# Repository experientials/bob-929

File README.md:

# Bob

Bob is an independent device that sees and senses the environment. It recognises objects and behavior based on what it has been taught. You use it in the field to collect the vision of things. The collected vision is turned into Machine Vision Models that 
allows you to create real-world puzzles and games. This allows you to create physical games to be played with family and friends
only limited by your imagination.

<family playing dice game>

It receives stereo video input over 2 x 2-lane MIPI CSI2. Additionally it receives sensor input over I2C
for distance, color, brightness. The sensor inputs are processed and disected to identify objects, people and
behaviour. Ziloo can connect over USB to make the output available on your Laptop, Phone or the Internet.

## Machine Vision Camera

Bob can be used to capture things out in the world to learn how to recognising them in the future. You can do this simply by pressing the camera button on the side. While the button is pressed images will be captured of the thing. As you capture a thing from different angles and in different conditions the coverage will increase.

You could use a Smartphone or Professional camera to capture your training images. But you should capture images with a setup similar to what the Vision Model will be seeing when used.

### Camera Remote Control

Using a bluetooth module you can control Bob with a Smartphone App for capturing Visions.

### Facing the camera

You can show Bob an object and turn it around. Bob will capture the vision of the object for you to have later.

## Physical Game Development Kit

Example Board game Monopoly
Bob Store for Apps
Tutorial Videos

## Speaker Bundle

The bundle comes with a speaker module that you plug into Bob. This allows Bob to speak.
It also comes with 2 voices that allow the games to easily generate speach as part of the game mechanics.

## Games Bundle

The bundle comes with an Multiplayer Module that you plug into Bob to connecting it with Bob elsewhere to allow you to play with
more people. 
It comes with 5 fun games to play in your livingroom and garden.

## Professional level Edge Machine Vision; Batteries Included

To get the precision in Machine Vision powerful hardware is needed to run modern ML Models made with PyTorch and TensorFlow.
To run this you typically get a Development board that costs $300 - $400 and then add camera modules that cost $75 - $200.
This gives you very raw power, but it isn't made to be run on batteries. It draws much too much power.
We have made Bob from the beginning aimed at single Lithium-Ion cell voltage, and made it good at detecting when the save on
battery.

## Unattended Mode

Bob can run unattended to capture interesting visions based on what is already known. This means that it needs good privacy, allowing you to review what has been captured before it is potentially uploaded to cloud services. This is why Bob isn't connected to the Internet or WiFi by default. It can be made to run unattended and automatically upload data, but in order to do so you must plug in the networking hardware.

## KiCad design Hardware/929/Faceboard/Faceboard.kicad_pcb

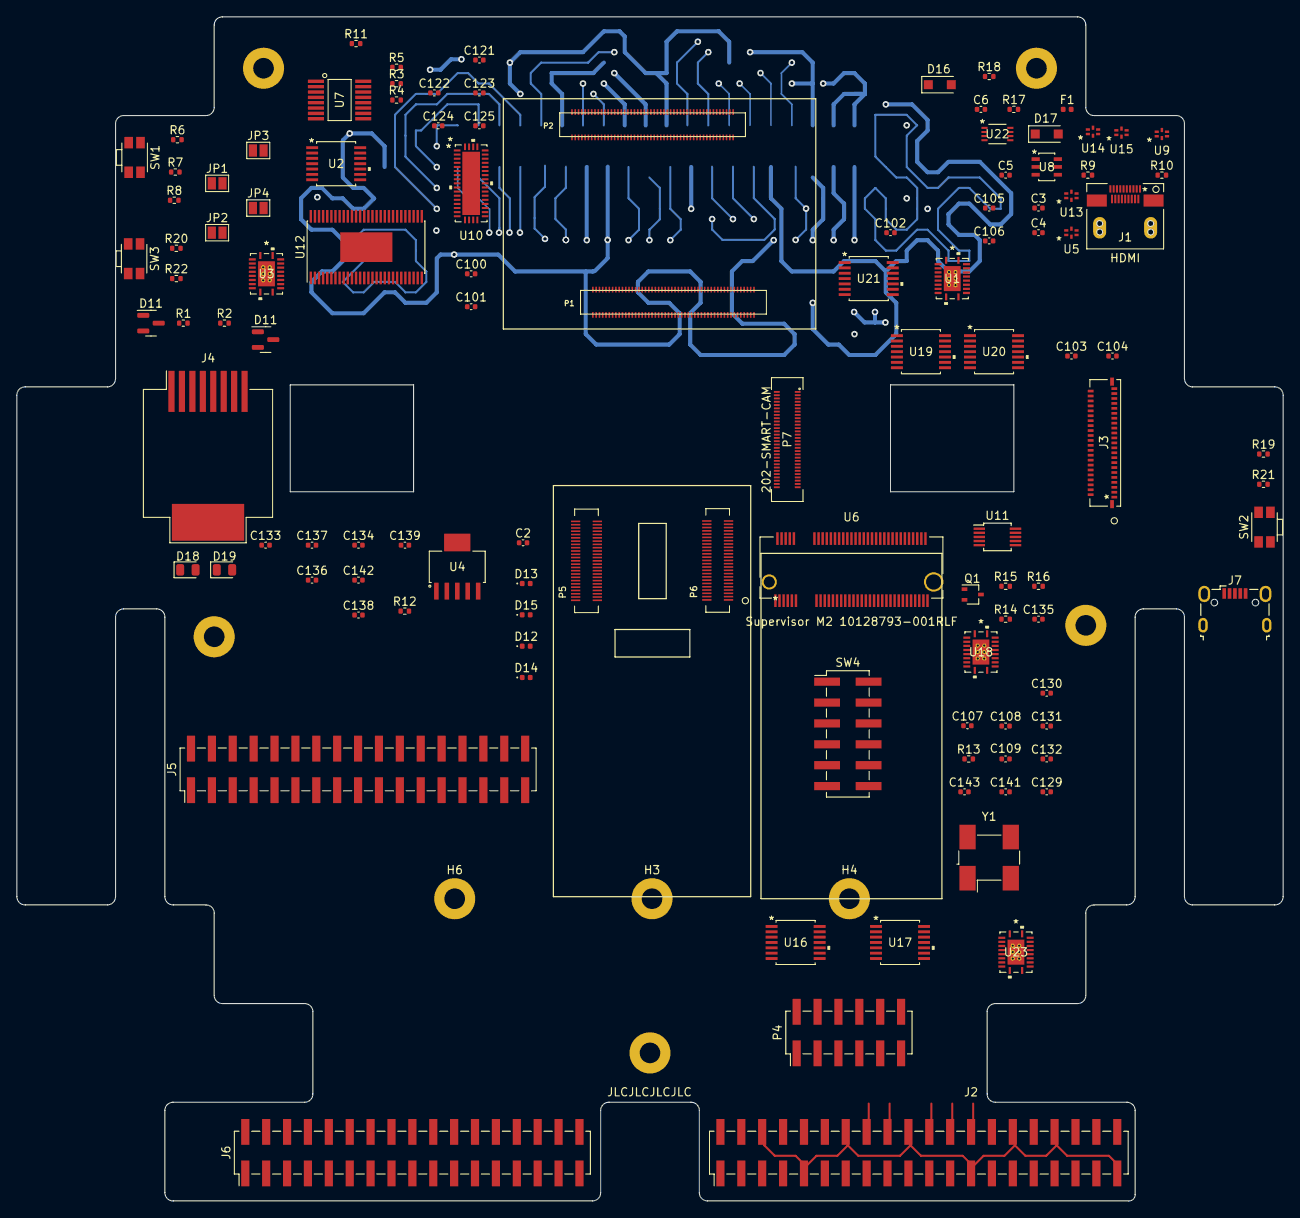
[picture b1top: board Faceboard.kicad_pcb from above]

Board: 4 copper layers, 154.0 x 144.0 mm, 122 parts (1 on the bottom side), 164 nets.

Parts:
C2: C; C_0402_1005Metric
C3, C4, C5, C121: 1uF; C_0402_1005Metric
C6, C100: 10nF; C_0402_1005Metric
C101, C102, C103, C104, C105, C106, C107, C108, C109, C122, C123, C124, C125, C133, C134, C141, C142: 100nF; C_0402_1005Metric
C129, C143: 27pF; C_0402_1005Metric
C130, C131, C137, C138, C139: 100uF; C_0402_1005Metric
C132, C136: 10uF; C_0402_1005Metric
C135: 100pF; C_0402_1005Metric
D11, D11#2: BAT54C; SOT-23
D12, D13, D14, D15: D; D_0402_1005Metric
D16, D17: 1A Schottky; D_SOD-123F
D18, D19: LED; LED_0805_2012Metric
F1: Polyfuse_Small; Fuse_0402_1005Metric
GPIO**: Front Face GPIO HEader; PinHeader_2x20_P2.54mm_Vertical_SMD
H1, H2, H3, H4, H5, H6, H7, H8: MountingHole; MountingHole_2.5mm_Pad
J1: HDMI; 467652301
J2: Raspberry_Pi_to_Ziloo; PinHeader_2x20_P2.54mm_Vertical_SMD
J3: Debug_4-2328724-5; 4-2328724-5
J4: RJ45; RJ45_Molex_0855135013_Vertical
J5: UCM-P20-misc; PinHeader_2x17_P2.54mm_Vertical_SMD
J6: UCM-P21-misc; PinHeader_2x17_P2.54mm_Vertical_SMD
J7: USB_B_Micro; USB_Micro-B_Wuerth_629105150521
JP1: TDO; SolderJumper-2_P1.3mm_Open_Pad1.0x1.5mm
JP2: TDI; SolderJumper-2_P1.3mm_Open_Pad1.0x1.5mm
JP3: SYS_SDA; SolderJumper-2_P1.3mm_Open_Pad1.0x1.5mm
JP4: SYS_SCL; SolderJumper-2_P1.3mm_Open_Pad1.0x1.5mm
P1: UCM-P1; HRS_DF40C-100DS-0.4V(51)
P2: UCM-P2; HRS_DF40C-100DS-0.4V(51)
P4: Power; PinHeader_2x06_P2.54mm_Vertical_SMD
P5: 292_PWRCTL-50; HRS_DF40C-50DS-0.4V(51)
P6: 292_HIGH-SPEED-50; HRS_DF40C-50DS-0.4V(51)
P7: 202-SMART-CAM; DF40C-60DS-0.4V51
Q1: 2SC4213; SOT-323_SC-70
R1, R2: 475Ohm; R_0402_1005Metric
R3, R4, R5: 10K; R_0402_1005Metric
R6, R8, R19, R20, R21, R22: 0R; R_0402_1005Metric
R7: DNP; R_0402_1005Metric
R9: 47K; R_0402_1005Metric
R10: 1K2; R_0402_1005Metric
R11: R; R_0402_1005Metric
R12: 10k; R_0402_1005Metric
R13: 1k; R_0402_1005Metric
R14: 100K; R_0402_1005Metric
R15, R16: 4.7K; R_0402_1005Metric
R17: 1K/1%; R_0402_1005Metric
R18: 200K; R_0402_1005Metric
SW1: Reset; SW_SPST_EVQP7A
SW2: Power; SW_SPST_EVQP7A
SW3: Alt. Boot; SW_SPST_EVQP7A
SW4: Power; PinHeader_2x06_P2.54mm_Vertical_SMD
U1, U3, U18, U23: SN74CB3Q3245RGYR
U2: SN74CBTLV3126PWR
U4: TPS79618DCQR
U5, U9, U13, U14, U15: LCFE121002H900TG
U6: Supervisor M2 10128793-001RLF; 10128793-001RLF
U7: TCA9534; TCA9534PWR
U8: IP4220CZ6
U10: CBTL04083ABS_518
U11: FSUSB42MUX; MSOP-10_3x3mm_P0.5mm
U12: Faceboard_Expander_FR2032IG56; HTSSOP-56-1EP_6.1x14mm_P0.5mm_EP3.61x6.35mm
U16, U17, U19, U20, U21: TXS0104EPWR
U22: PCA9306DCUR
Y1: 25.000MHz; Oscillator_SMD_Abracon_ASV-4Pin_7.0x5.1mm_HandSoldering

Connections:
/C_EX_RXD: P1.86 (UART4_TXD), U1.12 (B7)
/C_EX_TXD: P1.84 (UART4_RXD), U1.11 (B8)
/Camera + Sound Domain/I2S_1V8_RXC: P7.54 (I2S_SCK), U19.2 (A1)
/Camera + Sound Domain/I2S_1V8_RXD1: P7.50 (I2S_D1), U19.4 (A3)
/Camera + Sound Domain/I2S_1V8_RXD2: P7.48 (I2S_D2), U19.5 (A4)
/Camera + Sound Domain/I2S_1V8_RXFS: P7.52 (I2S_LRCLK), U19.3 (A2)
/Camera + Sound Domain/OE_SOUND: P7.41 (OE_SOUND), U19.8 (OE), U20.8 (OE), U21.8 (OE)
/Ethernet and SD1/ETH0_LED_1000: D11.1, D11#2.1
/Ethernet and SD1/ETH0_LINK_LED: D11.2, D11#2.2
/Ethernet and SD1/RPI_3V3: J2.1 (3V3), J2.17 (3V3), P4.10
/Ethernet and SD1/RPI_5V: J2.2 (5V), J2.4 (5V), P4.8
/Ethernet and SD1/SD1_CLK: J2.15 (GPIO22/SDIO_CLK), J5.15 (SD1_CLK)
/Ethernet and SD1/SD1_CMD: J2.16 (GPIO23/SDIO_CMD), J5.17 (SD1_CMD)
/Ethernet and SD1/SD1_DATA0: J2.18 (GPIO24/SDIO_DAT0), J5.24 (SD1_DATA0)
/Ethernet and SD1/SD1_DATA1: J2.22 (GPIO25/SDIO_DAT1), J5.22 (SD1_DATA1)
/Ethernet and SD1/SD1_DATA2: J2.37 (GPIO26/SDIO_DAT2), J5.21 (SD1_DATA2)
/Ethernet and SD1/SD1_DATA3: J2.13 (GPIO27/SDIO_DAT3), J5.23 (SD1_DATA3)
/Ethernet and SD1/STEM_I2C_SCL: J2.5 (STEM_SCL/GPIO3), J5.33 (STEM_SCL)
/Ethernet and SD1/STEM_I2C_SDA: J2.3 (STEM_SDA/GPIO2), J5.34 (STEM_SDA)
/Ethernet and SD1/SYS_I2C_SCL: J2.28 (SYS_SCL/GPIO1), J6.7 (SYS_I2C_SCL)
/Ethernet and SD1/SYS_I2C_SDA: J2.27 (SYS_SDA/GPIO0), J6.5 (SYS_I2C_SDA)
/Ethernet and SD1/SYS_PRG#: J5.30 (SYS_PRG), U23.19 (*OE)
/Ethernet and SD1/UCM_3V3: J5.7 (3V3), P4.4
/Ethernet and SD1/UCM_5V: J5.6 (5V0), P4.2
/Expander, M.2 and T-USB/3V3_TU: P5.40 (3V3), P5.43 (3V3), SW4.8
/Expander, M.2 and T-USB/5V_TU: P5.46 (5V), SW4.6
/Expander, M.2 and T-USB/ALT_BOOT: J3.19, R20.1, U12.10 (ALT_BOOT/P4.4)
/Expander, M.2 and T-USB/BAT_CE: P5.24 (BAT_CE#), U12.39 (P2.3)
/Expander, M.2 and T-USB/BAT_EN: P5.25 (BAT_EN), U12.38 (P2.4)
/Expander, M.2 and T-USB/BAT_INT: JP4.1 (A), P5.23 (BAT_INT)
/Expander, M.2 and T-USB/B_PCIE_WAKE: U7.6 (P2), U12.49 (B_PCIE_WAKE/P3.7)
/Expander, M.2 and T-USB/FACE_FW_RXD: J3.33, U12.27 (UART1_RX/FW_RX/A1/Vref+/P1.1)
/Expander, M.2 and T-USB/FACE_FW_TXD: J3.32, U12.28 (FW_TXD/A0/Vref-/P1.0)
/Expander, M.2 and T-USB/FACE_RST: J3.15, J3.31, U12.16 (~RST/NMI/SBWTDIO)
/Expander, M.2 and T-USB/FACE_SBWTCK: J3.30, U12.17 (TEST/SBWTCK)
/Expander, M.2 and T-USB/FACE_TCK: J3.11, JP4.2 (B), U12.24 (TCK/A4/VREF+/P1.4)
/Expander, M.2 and T-USB/FACE_TDI: J3.13, JP2.2 (B), U12.22 (TA0.2/TDI/TCLK/A6/P1.6)
/Expander, M.2 and T-USB/FACE_TDO: J3.14, JP1.2 (B), U12.21 (TA0.1/TDO/A7/P1.7)
/Expander, M.2 and T-USB/FACE_TMS: J3.12, JP3.2 (B), U12.23 (TMS/A5/P1.5)
/Expander, M.2 and T-USB/FLASH_HOLD: J3.5, P5.34 (FLASH_HOLD)
/Expander, M.2 and T-USB/F_SBWTCK: U3.2 (A1), U3.18 (B1)
/Expander, M.2 and T-USB/F_SBWTDIO: U3.3 (A2), U3.17 (B2)
/Expander, M.2 and T-USB/LOCK_BTN: P5.28 (LOCK_BTN), U12.9 (P4.5)
/Expander, M.2 and T-USB/M2B_PERST: U7.4 (P0), U12.56 (M2B_PERST/P3.0)
/Expander, M.2 and T-USB/M2B_USB_MUX: U7.9 (P4), U10.9 (SEL), U12.50 (M2B_USB_MUX/P3.6)
/Expander, M.2 and T-USB/M.2 Key B connector/PCIE_CLGEN_X1: C143.1, Y1.1
/Expander, M.2 and T-USB/M.2 Key B connector/PCIE_CLGEN_X2: C129.1, Y1.3
/Expander, M.2 and T-USB/MCU_SYS_INT: P5.12 (SYS_PD_CTL_INT), U12.13 (P4.1/XIN)
/Expander, M.2 and T-USB/PD_HRESET: J3.23, P5.39 (PD_HRESET), U12.35 (P2.7)
/Expander, M.2 and T-USB/PD_USBC_INT: P5.38 (USB1_PLUG_INT), U7.13 (~INT), U12.18 (TA1.1/P4.0)
/Expander, M.2 and T-USB/POR_B_3P3: R7.1, U12.40 (POR_B_3P3/P2.2)
/Expander, M.2 and T-USB/POWER_PD_CTL_INT: JP3.1 (A), P5.37 (POWER_PD_CTL_INT)
/Expander, M.2 and T-USB/POWER_SCL: J3.40, P5.36 (POWER_SCL), U2.2 (1A), U2.9 (3A), U12.5 (P7.1)
/Expander, M.2 and T-USB/POWER_SDA: J3.41, P5.35 (POWER_SDA), U2.5 (2A), U2.12 (4A), U12.4 (P7.2)
/Expander, M.2 and T-USB/POWER_TO_STEM: U2.10 (3OE), U2.13 (4OE), U12.19 (TA1.2/P8.3)
/Expander, M.2 and T-USB/POWER_TO_SYS: U2.1 (1OE), U2.4 (2OE), U12.20 (TA1CLK/P8.2)
/Expander, M.2 and T-USB/PWRBTN: J3.17, R19.1, U12.11 (PWRBTN/P4.3)
/Expander, M.2 and T-USB/PWR_CHARGE: D12.1 (K), P6.30 (PWR_CHARGE)
/Expander, M.2 and T-USB/PWR_CHARGE_LESS_1V4: D14.2 (A), U12.26 (CHARGE_LESS_1V4/UART1_TX/A2/P1.2)
/Expander, M.2 and T-USB/SBU1: J3.28, P5.9 (USB1_SBU1)
/Expander, M.2 and T-USB/SBU2: J3.29, P5.10 (USB1_SBU2)
/Expander, M.2 and T-USB/SHUTDOWN_BTN: P5.27 (SHUTDOWN_BTN), U12.8 (P4.6)
/Expander, M.2 and T-USB/SPI2_CLK: J3.1, P5.32 (SPI_CLK)
/Expander, M.2 and T-USB/SPI2_MISO: J3.2, P5.31 (SPI_MISO)
/Expander, M.2 and T-USB/SPI2_MOSI: J3.3, P5.30 (SPI_MOSI)
/Expander, M.2 and T-USB/STEM_I2C_SCL: J3.44, P6.17 (STEM_SCL), U2.8 (3B), U12.31 (UCB0SIMO/STEM_SCL/P5.3)
/Expander, M.2 and T-USB/STEM_I2C_SDA: J3.45, P6.18 (STEM_SDA), U2.11 (4B), U12.32 (UCB0SIMO/STEM_SDA/P5.2)
/Expander, M.2 and T-USB/STEM_INT: P6.19 (STEM_MSG), U12.12 (P4.2/XOUT)
/Expander, M.2 and T-USB/SYS_I2C_SCL: J3.42, P5.13 (SYS_I2C_SCL), U2.3 (1B), U7.14 (SCL), U12.33 (UCB0CLK/SYS_SCL/P5.1)
/Expander, M.2 and T-USB/SYS_I2C_SDA: J3.43, P5.14 (SYS_I2C_SDA), U2.6 (2B), U7.15 (SDA), U12.34 (UCB0STE/SYS_SDA/P5.0)
/Expander, M.2 and T-USB/SYS_RST_PMIC: J3.18, R6.1, U12.7 (SYS_RST_PMIC/P4.7)
/Expander, M.2 and T-USB/T-USB_SPI_CS: J3.4, P5.33 (SPI_CS), U12.36 (T-USB_SPI_CS/P2.6)
/Expander, M.2 and T-USB/T_SBWTCK: U3.6 (A5), U3.14 (B5)
/Expander, M.2 and T-USB/T_SBWTDIO: U3.7 (A6), U3.13 (B6)
/Expander, M.2 and T-USB/USB_XD_OE: P5.16 (USB_XD_OE), U12.52 (SH1_STCP/P3.4)
/Expander, M.2 and T-USB/USB_XD_SEL: P5.17 (USB_XD_SEL), U12.51 (SH2_STCP/P3.5)
/Expander, M.2 and T-USB/VCC_RTC_TU: P5.49 (VCC_RTC), SW4.10
/Expander, M.2 and T-USB/VSOM_LESS_1V4: D15.2 (A), U12.25 (VSOM_LESS_1V4/A3/P1.3)
/Expander, M.2 and T-USB/VSOM_TU: P5.1 (VSOM), P5.15 (VSOM), P5.26 (VSOM), P6.1 (VSOM), P6.26 (VSOM), P6.36 (VSOM), P6.39 (VSOM), P6.42 (VSOM), P6.45 (VSOM), P6.48 (VSOM), SW4.2, SW4.4
/F_EX_RXD: P1.74 (UART2_TXD), U1.16 (B3)
/F_EX_TXD: P1.76 (UART2_RXD), U1.15 (B4)
/HDMI socket/5V_POWER: C6.1, D17.1 (K), J1.19 (+5V_POWER), R9.1, R10.1, R17.1, R18.1, U8.1 (I/O_1), U8.5 (VP)
/HDMI socket/DDC_SCL: J1.17 (SCL), U8.4 (I/O_3), U22.6 (SCL2)
/HDMI socket/DDC_SDA: J1.18 (SDA), U8.3 (I/O_2), U22.5 (SDA2)
/HDMI socket/HDMI_CEC: D16.1 (K), J1.15 (CEC), U8.6 (I/O_4)
/I2C5_SCL: P1.100 (I2C5_SCL), U1.18 (B1)
/I2C5_SDA: P1.96 (I2C5_SDA), U1.17 (B2)
/I2C6_SCL: P1.87 (I2C6_SCL), U1.14 (B5)
/I2C6_SDA: P1.89 (I2C6_SDA), U1.13 (B6)
/SYS_PRG#: P2.69 (SYS_PRG#/4_17), U1.19 (*OE)
CAM_1V8: C103.1, C105.1, C107.1, P7.12 (1V8), P7.30 (1V8), U4.4 (OUT), U19.14 (VCCB), U20.14 (VCCB), U21.14 (VCCB)
GND: C5.2, C6.2, C100.2, C101.2, C102.1, C103.2, C104.2, C105.2, C106.2, C107.2, C108.2, C109.2, C121.1, C122.1, C123.1, C124.1, C125.1, C129.2, C130.2, C131.2, C132.2, C133.2, C134.2, C135.2, C136.2, C137.2, C138.2, C139.2, C141.2, C142.2, C143.2, J1.4 (TMDS_DATA2_SHIELD), J1.7 (TMDS_DATA1_SHIELD), J1.10 (TMDS_DATA0_SHIELD), J1.13 (TMDS_CLOCK_SHIELD), J2.6 (GND), J2.9 (GND), J2.14 (GND), J2.20 (GND), J2.25 (GND), J2.30 (GND), J2.34 (GND), J2.39 (GND), J3.7, J3.10, J5.31 (GND), J5.32 (GND), J6.6 (GND), J6.9 (GND), J7.5 (GND), J7.6 (Shield), P1.4 (GND), P1.10 (GND), P1.20 (GND), P1.40 (GND), P1.54 (GND), P1.64 (GND), P1.78 (GND), P1.88 (GND), P2.10 (GND), P2.16 (GND), P2.22 (GND), P2.28 (GND), P2.34 (GND), P2.40 (GND), P2.46 (GND), P2.54 (GND), P2.72 (GND), P2.82 (GND), P4.11, P4.12, P5.2 (GND), P5.5 (GND), P5.8 (GND), P5.11 (GND), P6.4 (GND), P6.7 (GND), P6.10 (GND), P6.13 (GND), P6.16 (GND), P6.20 (GND), P6.23 (GND), P6.33 (GND), Q1.2 (E), R1.2, R2.2, R4.2, R8.2, R9.2, R16.2, R17.2, R21.2, SW4.11, SW4.12, U1.10 (GND), U2.7 (GND), U3.10 (GND), U4.3 (GND), U5.5, U5.6, U6.3 (GND), U6.5 (GND), U6.27 (GND), U6.33 (GND), U6.39 (GND), U6.45 (GND), U6.51 (GND), U6.57 (GND), U7.8 (GND), U8.2 (GND), U9.5, U9.6, U10.1 (GND), U10.4 (GND), U10.10 (GND), U10.21 (GND), U10.39 (GND), U10.41 (XSD01), U10.43 (GND), U11.5 (GND), U11.10 (~OE), U12.14 (DVSS), U13.5, U13.6, U14.5, U14.6, U15.5, U15.6, U16.7 (GND), U17.7 (GND), U18.10 (GND), U19.7 (GND), U20.7 (GND), U21.7 (GND), U22.1 (GND), U23.10 (GND), Y1.2, Y1.4
HDMI_5V: F1.1, P4.1, P4.7, SW4.5
LIVE_1V8: C133.1, C141.1, U16.14 (VCCB), U17.14 (VCCB)
LIVE_3V3: C121.2, C122.2, C123.2, C124.2, C125.2, C130.1, C131.1, C132.1, C134.1, C136.1, C137.1, C138.1, C139.1, C142.1, D16.2 (A), P4.3, P4.9, R3.1, R5.1, R11.1, R12.2, R13.2, R14.1, R22.1, SW4.7, U6.2 (3V3), U6.70 (3V3), U6.72 (3V3), U6.74 (3V3), U7.16 (VDD), U10.5 (VDD), U10.8 (VDD), U10.13 (VDD), U10.18 (VDD), U10.20 (VDD), U10.30 (VDD), U10.40 (VDD), U10.42 (VDD), U11.1 (VCC), U16.1 (VCCA), U17.1 (VCCA), U18.20 (VCC), U22.2 (VREF1)
unnamed: C2.1, U4.5 (NR/FB)
unnamed: C3.2, R10.2, U5.2
unnamed: C4.2, U5.1
unnamed: C5.1, D17.2 (A), F1.2
unnamed: C102.2, P1.55 (PHY_2V5_OUT)
unnamed: C135.1, Q1.3 (C), R14.2, U6.67 (RESET)
unnamed: D11.3, D11#2.3, D19.2 (A)
unnamed: D12.2 (A), D14.1 (K)
unnamed: D13.2 (A), D15.1 (K)
unnamed: D18.1 (K), R1.1
unnamed: D19.1 (K), R2.1
unnamed: J1.1 (HOT_PLUG_DETECT), U5.3
unnamed: J1.2 (UTILITY), U5.4
unnamed: J1.3 (TMDS_DATA2+), U9.2
unnamed: J1.5 (TMDS_DATA2-), U9.1
unnamed: J1.6 (TMDS_DATA1+), U14.2
unnamed: J1.8 (TMDS_DATA1-), U14.1
unnamed: J1.9 (TMDS_DATA0+), U13.2
unnamed: J1.11 (TMDS_DATA0-), U13.1
unnamed: J1.12 (TMDS_CLOCK+), U15.2
unnamed: J1.14 (TMDS_CLOCK-), U15.1
unnamed: J2.8 (GPIO14/UART1_TXD), U23.4 (A3)
unnamed: J2.10 (GPIO15/UART1_RXD), U23.5 (A4)
unnamed: J2.32 (UART3_TX/GPIO12), U23.8 (A7)
unnamed: J2.33 (UART3_RX/GPIO13), U23.9 (A8)
unnamed: J3.24, P5.48 (USB1_XDP)
unnamed: J3.25, P5.47 (USB1_XDN)
unnamed: J3.26, P5.45 (USB2_XDP)
unnamed: J3.27, P5.44 (USB2_XDN)
unnamed: C100.1, C101.1, P1.62 (UCM_AVDD33_ETH)
unnamed: P5.6 (USB2_DP), U11.9 (HSD2+)
unnamed: P5.7 (USB2_DN), U11.8 (HSD2-)
unnamed: P6.8 (USB2_RX_DP), U10.38 (B0_P)
unnamed: P6.9 (USB2_RX_DN), U10.37 (B0_N)
unnamed: P6.11 (USB2_TX_DP), U10.36 (B1_P)
unnamed: P6.12 (USB2_TX_DN), U10.35 (B1_N)
unnamed: P7.5 (GND), P7.11 (GND), P7.17 (GND), P7.18 (GND), P7.23 (GND), P7.29 (GND), P7.56 (GND)
unnamed: Q1.1 (B), R15.2, R16.1
unnamed: R3.2, U7.3 (A2)
unnamed: R4.1, U7.1 (A0)
unnamed: R5.2, U7.2 (A1)
unnamed: R6.2, R7.2, SW1.1
unnamed: R8.1, SW1.2
unnamed: R11.2, U10.19 (XSD23)
unnamed: R12.1, U6.8 (W_DISABL1)
unnamed: R13.1, U6.6 (PWR_OFF)
unnamed: R18.2, U22.7 (VREF2), U22.8 (EN)
unnamed: R19.2, SW2.1
unnamed: R20.2, SW3.1
unnamed: R21.1, SW2.2
unnamed: R22.2, SW3.2
unnamed: U6.48 (GPIO_4), U16.2 (A1)
unnamed: U6.60 (COEX3), U16.3 (A2)
unnamed: U6.62 (M2B_UART_TXD), U16.4 (A3)
unnamed: U6.64 (M2B_UART_RXD), U16.5 (A4)
unnamed: U6.40 (STEM_SCL), U17.2 (A1)
unnamed: U6.42 (STEM_SDA), U17.3 (A2)
unnamed: U6.44 (GNSS_IRQ), U17.4 (A3)
unnamed: U6.46 (GPIO_3), U17.5 (A4)
unnamed: U6.56 (MFG_DAT), U18.11 (B8)
unnamed: U6.58 (MFG_CLK), U18.12 (B7)
unnamed: U6.66 (DETECT/CMD), U18.13 (B6)
unnamed: U6.68 (SUSCLK/SDCLK), U18.14 (B5)
unnamed: U6.65 (SD2_DATA3), U18.15 (B4)
unnamed: U6.63 (SD2_DATA2), U18.16 (B3)
unnamed: U6.61 (SD2_DATA1), U18.17 (B2)
unnamed: U6.59 (SD2_DATA0), U18.18 (B1)
SLEEP_3V3: C104.1, C106.1, C108.1, J3.16, J3.20, P1.93 (VCC_RTC), P7.6 (3V3), P7.24 (3V3), SW4.9, U1.20 (VCC), U2.14 (VCC), U4.1 (EN), U4.2 (IN), U19.1 (VCCA), U20.1 (VCCA), U21.1 (VCCA), U23.20 (VCC)
VSOM: D13.1 (K), P1.11 (V_SOM), P1.27 (V_SOM), P1.43 (V_SOM), P1.57 (V_SOM), P1.69 (V_SOM), P1.83 (V_SOM), P2.9 (V_SOM), P2.19 (V_SOM), P2.29 (V_SOM), P2.39 (V_SOM), P2.57 (V_SOM), P2.71 (V_SOM), P2.87 (V_SOM), SW4.1, SW4.3

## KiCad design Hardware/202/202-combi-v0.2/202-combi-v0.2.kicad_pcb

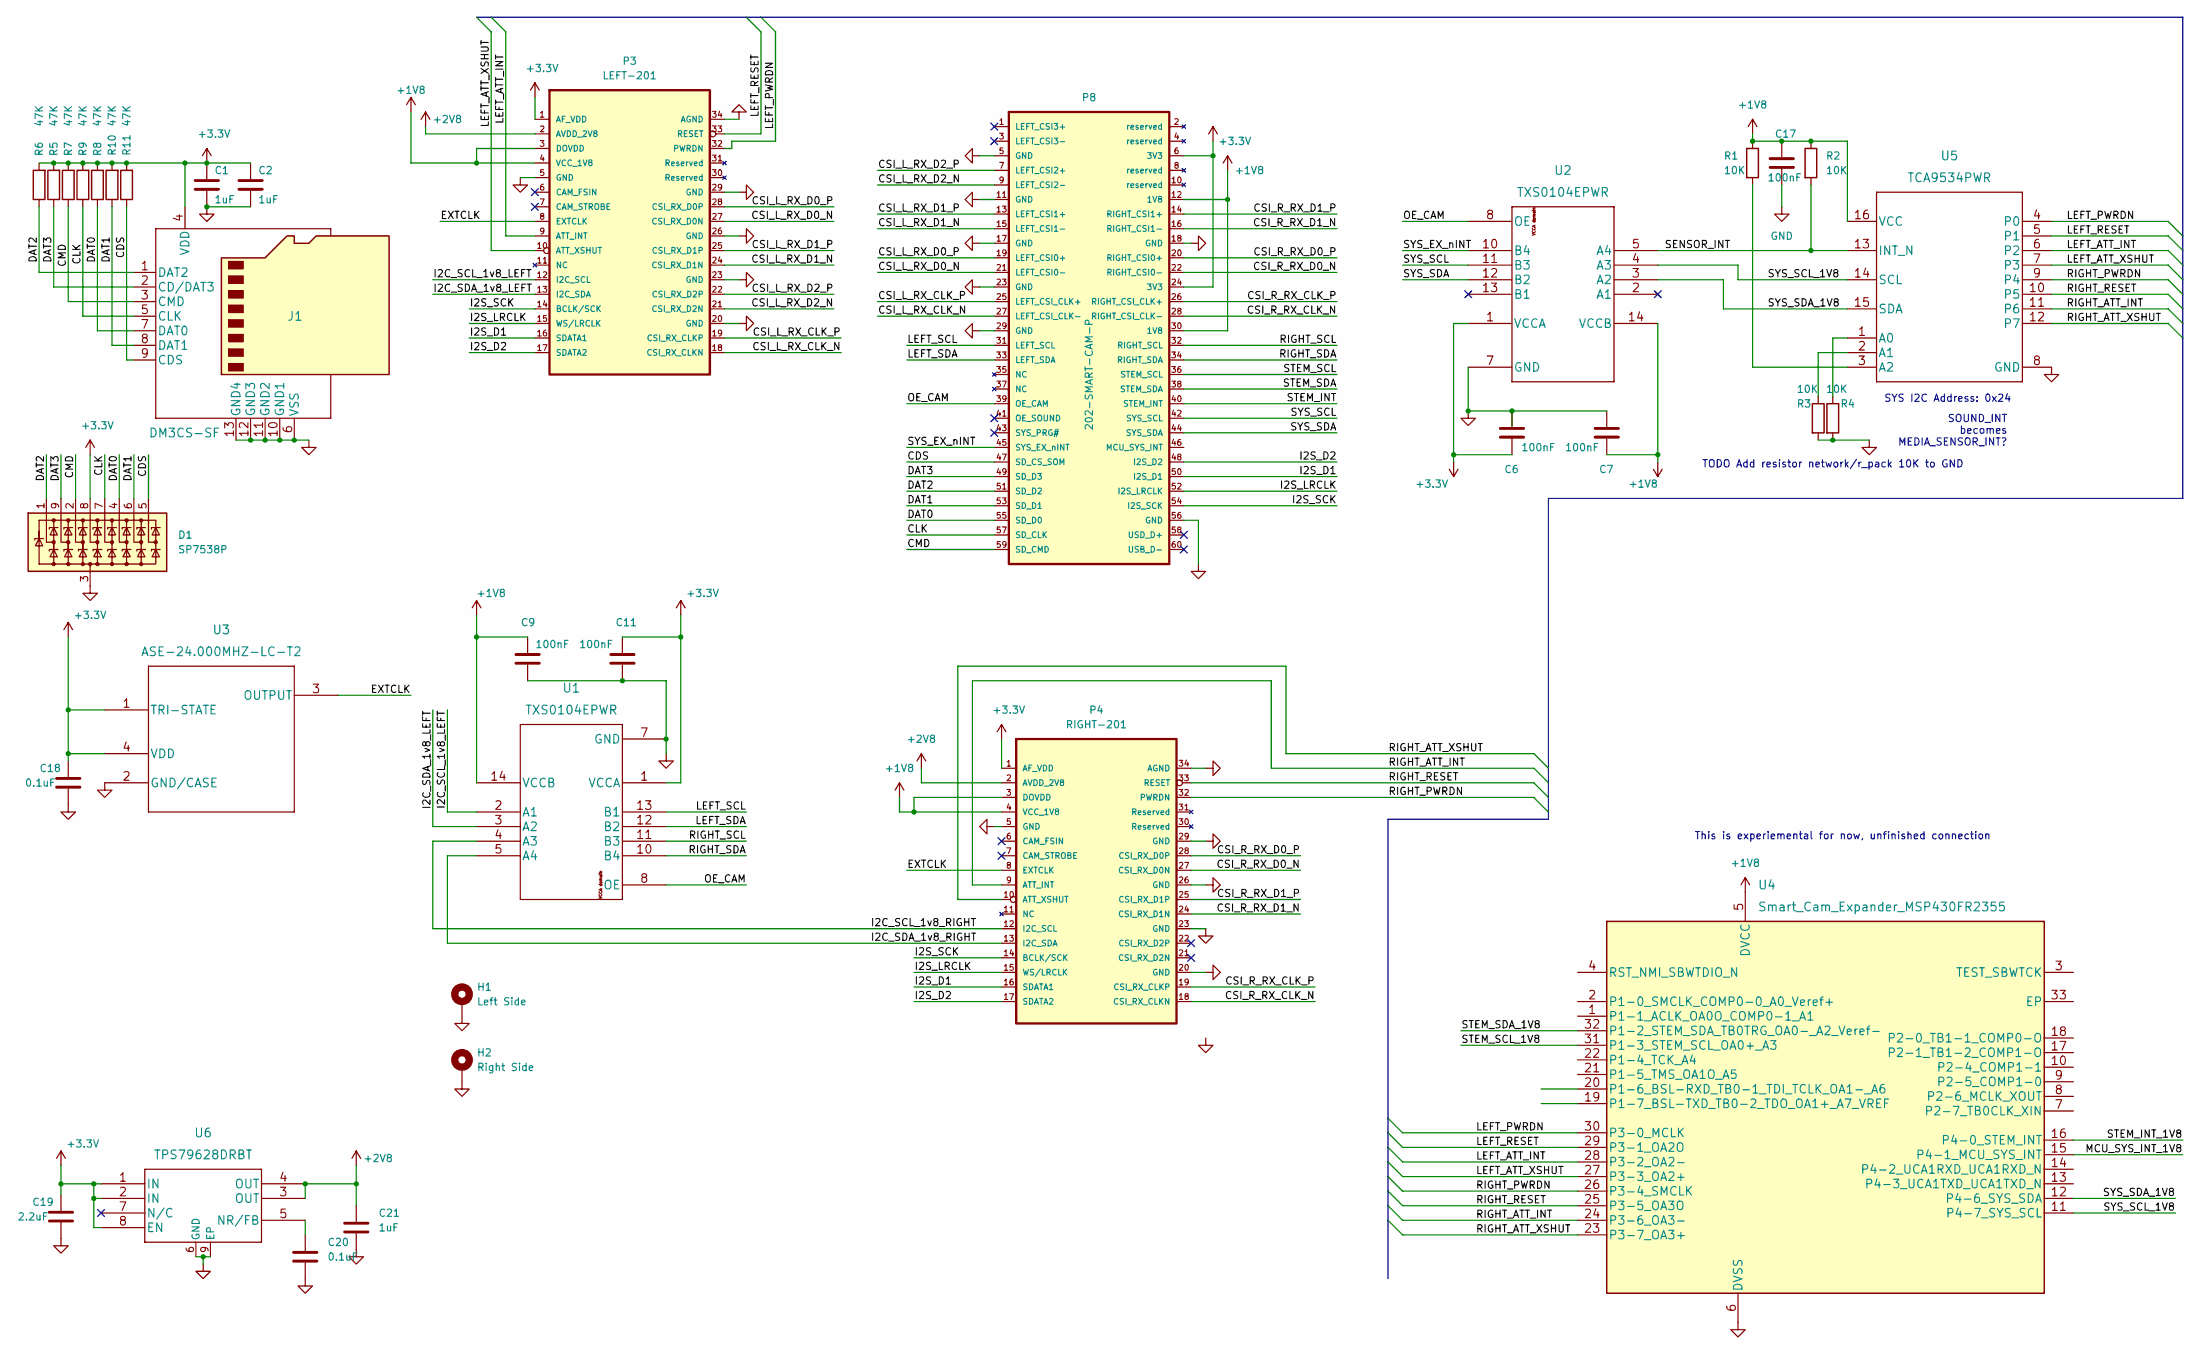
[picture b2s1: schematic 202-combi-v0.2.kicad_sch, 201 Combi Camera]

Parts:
C1, C2, C21: 1uF; C_0402_1005Metric
C6, C7, C9, C11, C17: 100nF; C_0402_1005Metric
C18, C20: 0.1uF; C_0402_1005Metric
C19: 2.2uF; C_0402_1005Metric
D1: SP7538P; UDFN-9_1.0x3.8mm_P0.5mm
H1: Left Side; MountingHole_2.2mm_M2
H2: Right Side; MountingHole_2.2mm_M2
J1: DM3CS-SF
P3: LEFT-201; HIROSE_DF40C-34DS-0.4V(51)_corrected
P4: RIGHT-201; HIROSE_DF40C-34DS-0.4V(51)_corrected
P8: 202-SMART-CAM-P; DF40C-60DP-0.4V51
R1, R2, R3, R4: 10K; R_0402_1005Metric
R5, R6, R7, R8, R9, R10, R11: 47K; R_0402_1005Metric
U1, U2: TXS0104EPWR; SSOP-14_5.3x6.2mm_P0.65mm
U3: ASE-24.000MHZ-LC-T2
U4: Smart_Cam_Expander_MSP430FR2355; MSP430FR2355TRSMR
U5: TCA9534PWR
U6: TPS79628DRBT; DFN-8-1EP_3x3mm_P0.65mm_EP1.7x2.05mm

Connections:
+1V8: C7.1, C9.1, C17.2, P3.3 (DOVDD), P3.4 (VCC_1V8), P4.3 (DOVDD), P4.4 (VCC_1V8), P8.12 (1V8), P8.30 (1V8), R1.1, R2.1, U1.14 (VCCB), U2.14 (VCCB), U4.5 (DVCC), U5.16 (VCC)
+2V8: C21.1, P3.2 (AVDD_2V8), P4.2 (AVDD_2V8), U6.3 (OUT), U6.4 (OUT)
+3.3V: C1.2, C2.2, C6.1, C11.1, C18.1, C19.1, D1.8 (K7), J1.4 (VDD), P3.1 (AF_VDD), P4.1 (AF_VDD), P8.6 (3V3), P8.24 (3V3), R5.2, R6.2, R7.2, R8.2, R9.2, R10.2, R11.2, U1.1 (VCCA), U2.1 (VCCA), U3.1 (TRI-STATE), U3.4 (VDD), U6.1 (IN), U6.2 (IN), U6.8 (EN)
/CDS: D1.5 (K4), J1.9 (CDS), P8.47 (SD_CS_SOM), R11.1
/CLK: D1.7 (K6), J1.5 (CLK), P8.57 (SD_CLK), R8.1
/CMD: D1.2 (K2), J1.3 (CMD), P8.59 (SD_CMD), R7.1
/CSI_L_RX_CLK_N: P3.18 (CSI_RX_CLKN), P8.27 (LEFT_CSI_CLK-)
/CSI_L_RX_CLK_P: P3.19 (CSI_RX_CLKP), P8.25 (LEFT_CSI_CLK+)
/CSI_L_RX_D0_N: P3.27 (CSI_RX_D0N), P8.21 (LEFT_CSI0-)
/CSI_L_RX_D0_P: P3.28 (CSI_RX_D0P), P8.19 (LEFT_CSI0+)
/CSI_L_RX_D1_N: P3.24 (CSI_RX_D1N), P8.15 (LEFT_CSI1-)
/CSI_L_RX_D1_P: P3.25 (CSI_RX_D1P), P8.13 (LEFT_CSI1+)
/CSI_L_RX_D2_N: P3.21 (CSI_RX_D2N), P8.9 (LEFT_CSI2-)
/CSI_L_RX_D2_P: P3.22 (CSI_RX_D2P), P8.7 (LEFT_CSI2+)
/CSI_R_RX_CLK_N: P4.18 (CSI_RX_CLKN), P8.28 (RIGHT_CSI_CLK-)
/CSI_R_RX_CLK_P: P4.19 (CSI_RX_CLKP), P8.26 (RIGHT_CSI_CLK+)
/CSI_R_RX_D0_N: P4.27 (CSI_RX_D0N), P8.22 (RIGHT_CSI0-)
/CSI_R_RX_D0_P: P4.28 (CSI_RX_D0P), P8.20 (RIGHT_CSI0+)
/CSI_R_RX_D1_N: P4.24 (CSI_RX_D1N), P8.16 (RIGHT_CSI1-)
/CSI_R_RX_D1_P: P4.25 (CSI_RX_D1P), P8.14 (RIGHT_CSI1+)
/DAT0: D1.4 (K3), J1.7 (DAT0), P8.55 (SD_D0), R9.1
/DAT1: D1.6 (K5), J1.8 (DAT1), P8.53 (SD_D1), R10.1
/DAT2: D1.1 (K1), J1.1 (DAT2), P8.51 (SD_D2), R5.1
/DAT3: D1.9 (K8), J1.2 (CD/DAT3), P8.49 (SD_D3), R6.1
/EXTCLK: P3.8 (EXTCLK), P4.8 (EXTCLK), U3.3 (OUTPUT)
/I2C_SCL_1v8_LEFT: P3.12 (I2C_SCL), U1.2 (A1)
/I2C_SCL_1v8_RIGHT: P4.12 (I2C_SCL), U1.4 (A3)
/I2C_SDA_1v8_LEFT: P3.13 (I2C_SDA), U1.3 (A2)
/I2C_SDA_1v8_RIGHT: P4.13 (I2C_SDA), U1.5 (A4)
/I2S_D1: P3.16 (SDATA1), P4.16 (SDATA1), P8.50 (I2S_D1)
/I2S_D2: P3.17 (SDATA2), P4.17 (SDATA2), P8.48 (I2S_D2)
/I2S_LRCLK: P3.15 (WS/LRCLK), P4.15 (WS/LRCLK), P8.52 (I2S_LRCLK)
/I2S_SCK: P3.14 (BCLK/SCK), P4.14 (BCLK/SCK), P8.54 (I2S_SCK)
/LEFT_ATT_INT: P3.9 (ATT_INT), U4.28 (P3-2_OA2-), U5.6 (P2)
/LEFT_ATT_XSHUT: P3.10 (ATT_XSHUT), U4.27 (P3-3_OA2+), U5.7 (P3)
/LEFT_PWRDN: P3.32 (PWRDN), U4.30 (P3-0_MCLK), U5.4 (P0)
/LEFT_RESET: P3.33 (RESET), U4.29 (P3-1_OA2O), U5.5 (P1)
/LEFT_SCL: P8.31 (LEFT_SCL), U1.13 (B1)
/LEFT_SDA: P8.33 (LEFT_SDA), U1.12 (B2)
/MCU_SYS_INT_1V8: U4.15 (P4-1_MCU_SYS_INT)
/OE_CAM: P8.39 (OE_CAM), U1.8 (OE), U2.8 (OE)
/RIGHT_ATT_INT: P4.9 (ATT_INT), U4.24 (P3-6_OA3-), U5.11 (P6)
/RIGHT_ATT_XSHUT: P4.10 (ATT_XSHUT), U4.23 (P3-7_OA3+), U5.12 (P7)
/RIGHT_PWRDN: P4.32 (PWRDN), U4.26 (P3-4_SMCLK), U5.9 (P4)
/RIGHT_RESET: P4.33 (RESET), U4.25 (P3-5_OA3O), U5.10 (P5)
/RIGHT_SCL: P8.32 (RIGHT_SCL), U1.11 (B3)
/RIGHT_SDA: P8.34 (RIGHT_SDA), U1.10 (B4)
/SENSOR_INT: R2.2, U2.5 (A4), U5.13 (INT_N)
/STEM_INT: P8.40 (STEM_INT)
/STEM_INT_1V8: U4.16 (P4-0_STEM_INT)
/STEM_SCL: P8.36 (STEM_SCL)
/STEM_SCL_1V8: U4.31 (P1-3_STEM_SCL_OA0+_A3)
/STEM_SDA: P8.38 (STEM_SDA)
/STEM_SDA_1V8: U4.32 (P1-2_STEM_SDA_TB0TRG_OA0-_A2_Veref-)
/SYS_EX_nINT: P8.45 (SYS_EX_nINT), U2.10 (B4)
/SYS_SCL: P8.42 (SYS_SCL), U2.11 (B3)
/SYS_SCL_1V8: U2.4 (A3), U4.11 (P4-7_SYS_SCL), U5.14 (SCL)
/SYS_SDA: P8.44 (SYS_SDA), U2.12 (B2)
/SYS_SDA_1V8: U2.3 (A2), U4.12 (P4-6_SYS_SDA), U5.15 (SDA)
GND: C1.1, C2.1, C6.2, C7.2, C9.2, C11.2, C17.1, C18.2, C19.2, C20.2, C21.2, D1.3 (A), H1.1, H2.1, J1.6 (VSS), J1.10 (GND1), J1.11 (GND2), J1.12 (GND3), J1.13 (GND4), P3.5 (GND), P3.20 (GND), P3.23 (GND), P3.26 (GND), P3.29 (GND), P3.34 (AGND), P4.5 (GND), P4.20 (GND), P4.23 (GND), P4.26 (GND), P4.29 (GND), P4.34 (AGND), P8.5 (GND), P8.11 (GND), P8.17 (GND), P8.18 (GND), P8.23 (GND), P8.29 (GND), P8.56 (GND), R3.2, R4.2, U1.7 (GND), U2.7 (GND), U3.2 (GND/CASE), U4.6 (DVSS), U4.33 (EP), U5.8 (GND), U6.6 (GND), U6.9 (EP)
unnamed: C20.1, U6.5 (NR/FB)
unnamed: R1.2, U5.3 (A2)
unnamed: R3.1, U5.2 (A1)
unnamed: R4.1, U5.1 (A0)

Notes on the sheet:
SOUND_INT becomes MEDIA_SENSOR_INT?
SYS I2C Address: 0x24
TODO Add resistor network/r_pack 10K to GND
This is experiemental for now, unfinished connection

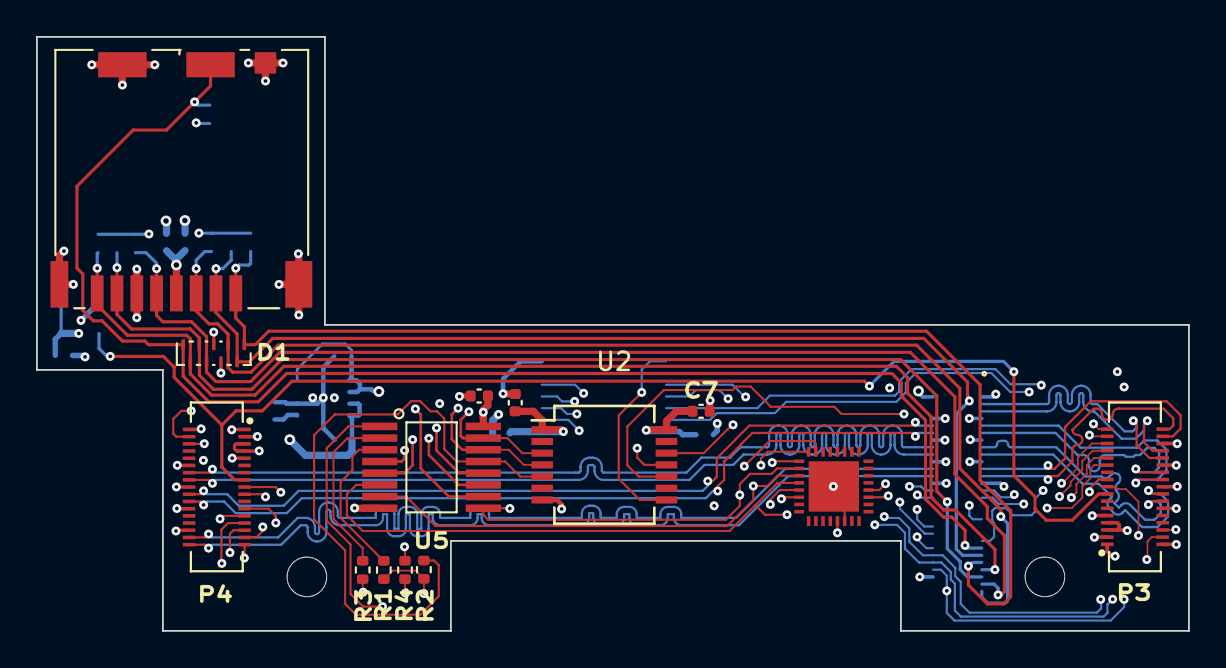
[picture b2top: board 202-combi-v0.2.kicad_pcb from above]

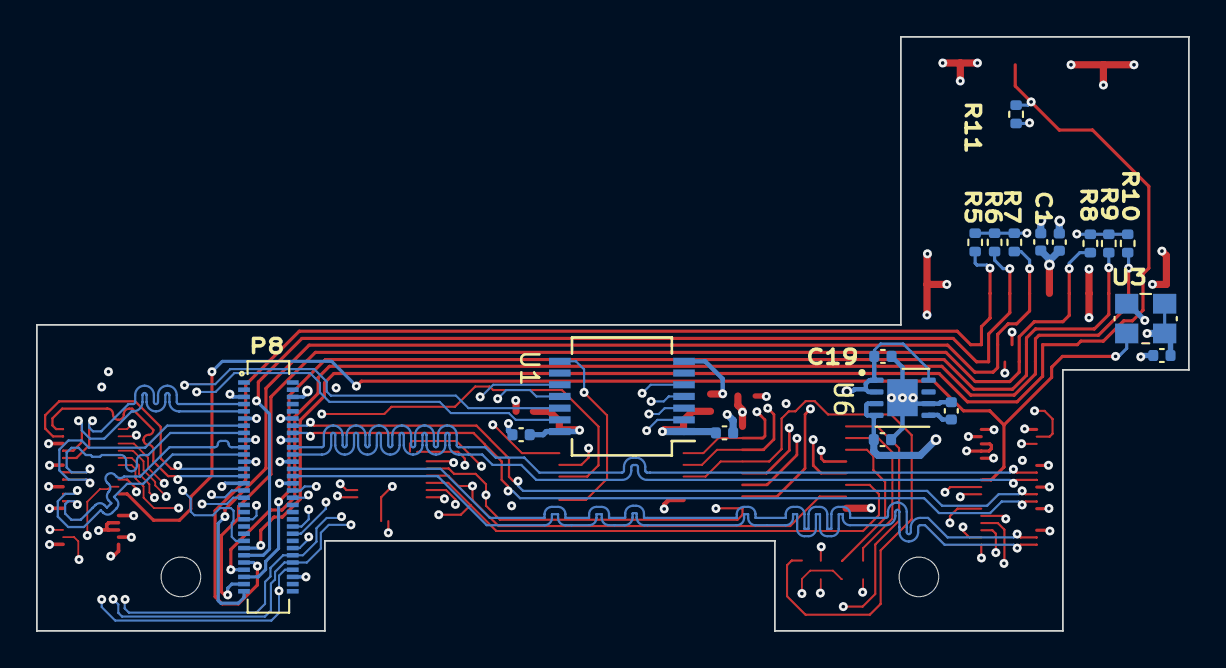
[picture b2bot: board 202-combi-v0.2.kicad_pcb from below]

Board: 6 copper layers, 64.0 x 33.0 mm, 35 parts (19 on the bottom side), 57 nets.

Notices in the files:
parts and their libraries:
Copyright 2021 Accelerated Designs. All rights reserved.
